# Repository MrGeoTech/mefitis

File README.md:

# Mefitis

The sensor data gathering and presenting software suite for NDSU's Bison Pullers. Named after the 
roman goddess of poisonous gasses, this platform allows us to measure sensors all over the tractor.
We use this data to improve many aspects of the tractor, including emissions and noise.

## Database Design

Database name: `data`  
Each row represents one seconds worth of data. The columns are for each different sensor.

The current sensors are as follows:  
`Sound_Engine`, `Sound_Operator`, `Emissions_Engine`, `Emissions_Operator`, `Temp_Engine`, `Temp_Exhaust`, `RPM`

## Arduino Uno 3

#### Installing

Pre-req: `arduino-cli`

You can either install the software from the pi or from any other computer. Start by going into the
`arduino` directory.

Next, compile and upload the code:

```bash
sudo arduino-cli compile --fqbn arduino:avr:uno arduino.ino
sudo arduino-cli upload -p /dev/ttyACM0 --fqbn arduino:avr:uno arduino.ino
```

Now simply plug in the arduino to the pi, start the webserver, and everything should be working.

## Raspberry Pi

#### Installation

To install of a raspberry pi, first, install Raspbian Minimal 64-bit OS onto the SD card. Make sure that the username
is `pullers`.

Next, make sure to update the system and then install `git` and `postgresql`.

```bash
sudo apt update
sudo apt upgrade
sudo apt install -y git postgresql libpg-dev
sudo apt autoremove
```

Next, configure `postgresql` by running `sudo -u postgres psql`. This should take you to a SQL shell.
To configure from there, first create a new database called `data`.

```sql
CREATE TABLE IF NOT EXISTS data (id SERIAL PRIMARY KEY, Sound_Engine REAL, Sound_Operator REAL, Emissions_Engine REAL, Emissions_Operator REAL, Temp_Engine REAL, Temp_Exhaust REAL, RPM INTEGER);
```

Then set the postgres user password.

```sql
ALTER USER postgres with encrypted password 'postgres';
```

You should now be able to exit the SQL shell. Next, setup configure git with whatever username and 
email you want. Now, you will have to install nix. To do this, simply run `sh <(curl -L https://nixos.org/nix/install) --daemon`.
You should be able to just follow the prompts and it should install nicely.

After installing nix, restart the system.

Now, download the git repo into the home folder using `git clone https://github.com/MrGeoTech/mefitis.git`.

Finally, setup a python venv at `~/venv`. Make sure to add the following python packages:
`w1thermsensor[async] pyserial psycopg2 gpiozero RPi.GPIO`

#### Running

To run the program on the pi, first go into the `pi` directory and run `nix-shell`. This should
setup the environment to run the server in. Next, just run `sh ./run.sh` and everything should start.

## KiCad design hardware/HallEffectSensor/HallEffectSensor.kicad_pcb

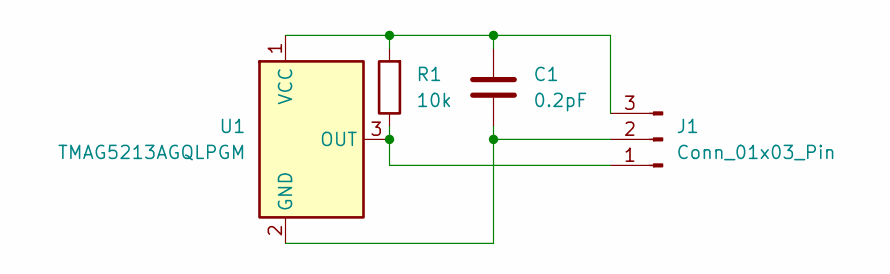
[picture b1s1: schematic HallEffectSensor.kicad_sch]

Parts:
C1: 0.2pF; C_0402_1005Metric
J1: Conn_01x03_Pin; PinHeader_1x03_P2.54mm_Horizontal
R1: 10k; R_0603_1608Metric
U1: TMAG5213AGQLPGM; TO-92_Inline

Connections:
unnamed: J1.1, R1.1, U1.3 (OUT)
unnamed: C1.2, J1.2, U1.2 (GND)
unnamed: C1.1, J1.3, R1.2, U1.1 (VCC)

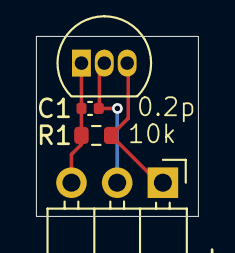
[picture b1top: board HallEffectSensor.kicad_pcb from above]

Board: 2 copper layers, 9.0 x 10.0 mm, 4 parts (0 on the bottom side), 3 nets.

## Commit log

2025-03-13 Add run script and serial monitor for testing.
2025-03-13 Update run file
2025-03-13 Update running to hopefully work
2025-03-13 Fix run.sh again...
2025-03-13 Change system to now work and delete irrelevant files
2025-03-13 Update sensors
2025-03-13 More sensors.py changes
2025-03-13 Update again
2025-03-13 Locking in baud rate and trying to make sensors.py work
2025-03-13 More updates to sensors
2025-03-13 Fix sensors
2025-03-13 Remove commented out code
2025-03-13 Change to using postgres
2025-03-13 Update credentials
2025-03-13 Update shell environment for python
2025-03-13 Update shell correctly...
2025-03-13 Fix run.sh to work with postgres
2025-03-14 Add debugging
2025-03-14 Trying to fix not updating the databse
2025-03-14 Trying duplicating logic to test
2025-03-14 Update test
2025-03-14 Fix spelling
2025-03-14 Update names
2025-03-14 More print debugging
2025-03-14 Fix mistake
2025-03-14 Try fixing get_temp_data
2025-03-14 Remove debugging prints
2025-03-14 Update to format data properly
2025-03-22 A lot more testing stuff
2025-03-22 Update test sensors
2025-03-22 Configure therm sensor connection
2025-03-24 Update shell env
2025-03-24 Update shell
2025-03-24 Run sensors.py as root
2025-03-24 Update shell.nix to be only a dev environment
2025-03-24 Add GPIO
2025-03-24 Comment out serial part for testing
2025-03-24 Made temp sensing more resiliant to failures
2025-03-24 Update run.sh and readme
2025-03-24 Fix syntax
2025-03-24 Use actual python syntax
2025-03-24 Add some print debugging
2025-03-24 Debugging
2025-03-24 More debugging
2025-03-24 Try fixing it
2025-03-24 Print debugging
2025-03-24 Move get_sensors to get_temp_data
2025-03-24 Update to asyncio for the temp data
2025-03-24 Update main function to be async
2025-03-24 Remove old code
2025-03-24 Update to be more resiliant to temp sensors failures
2025-03-24 Update temp sensing
2025-03-24 Update index correctly
2025-03-24 Uncomment arduino. Everything except for the RPM sensors has been tested and works
2025-03-24 Update sensors to convert sensor data to db
2025-03-24 Import numpy
2025-03-24 Fix dumb mistake
2025-03-24 Fix code again
2025-03-24 Update casting
2025-03-24 Update casting again
2025-03-24 Fix name
2025-03-24 Rearange a bit
2025-03-25 Start working on pcb for hall-effect sensors
2025-03-27 Update sensors to use one sensor
2025-03-28 Hopefully fix recoding issue
2025-03-28 Add some debugging
2025-03-28 Add some debouncing
2025-03-28 Change timings
2025-03-28 Fix getting time
2025-03-28 Another division?
2025-03-28 Switch to at least 10 us and use len(SENSORS)
2025-03-28 Remove Print
2025-03-28 Add global rpm
2025-03-28 Use correct constant
2025-03-28 Revert back to raw values. We'll just fix it in post
2025-04-03 Update to test new sound sensors
2025-04-04 Update rate
2025-04-04 Update to raw values
2025-04-07 Add printing devices
2025-04-07 Update test_sensors with correct device index
2025-04-07 Add no exception
2025-04-07 Update test_sensors
2025-04-07 Update global values
2025-04-07 Just use larger chunk size
2025-04-07 Remove chunk
2025-04-07 Remove if
2025-04-07 Update gpt code with stack overflow code...progress...
2025-04-07 Update test_sensors to display both channels
2025-04-07 Update number of dashes
2025-04-07 Remove prints
2025-04-07 Update sensors to use new sound sensors
2025-04-07 Update sound
2025-04-09 Disable serial for now
2025-04-09 Update sound gathering system
2025-04-09 Go back to default frames per buffer
2025-04-09 Use python floats
2025-04-10 Add conversion factor
2025-04-10 Change calibration method
2025-04-10 Go back to previous method
2025-04-10 Do python correctly..I think..
2025-04-10 Doing some testing
2025-04-10 Fix code
2025-04-10 Remove offset
2025-04-10 Revert changes
2025-04-10 Test calibrations
2025-04-10 Change correction factor
